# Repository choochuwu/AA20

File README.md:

# AA20
unsplit ortholinear "gaming" keyboard.
Like it's name sake, this isn't the greatest, but to me it is more comfortable for games compared to a column staggered board.

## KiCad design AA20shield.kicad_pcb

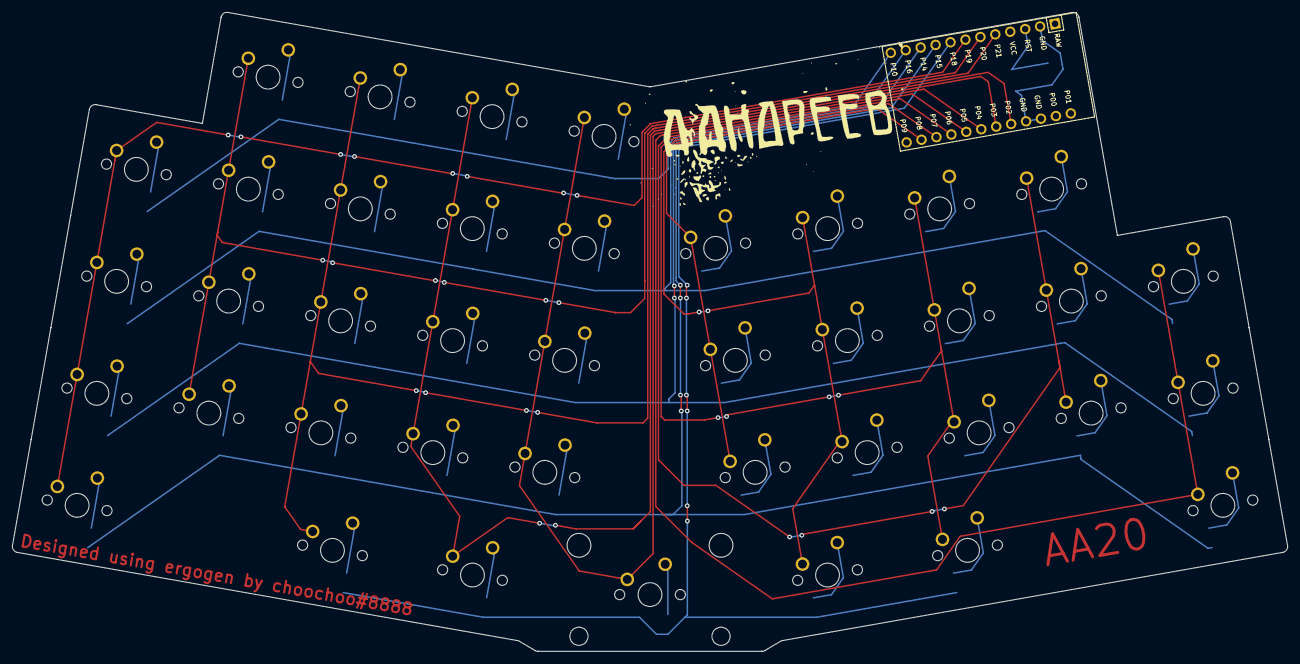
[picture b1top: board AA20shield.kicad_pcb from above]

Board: 2 copper layers, 213.6 x 107.0 mm, 82 parts (0 on the bottom side), 56 nets.

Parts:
B1: SW_TACT_ALPS_SKQGABE010
D1, D2, D3, D4, D5, D6, D7, D8, D9, D10, D11, D12, D13, D14, D15, D16, D17, D18, D19, D20, D21, D22, D23, D24, D25, D26, D27, D28, D29, D30, D31, D32, D33, D34, D35, D36, D37, D38, D39, D40: ComboDiode
MCU1: ProMicro
S1, S2, S3, S4, S5, S6, S7, S8, S9, S10, S11, S12, S13, S14, S15, S16, S17, S18, S19, S20, S21, S22, S23, S24, S25, S26, S27, S28, S29, S30, S31, S32, S33, S34, S35, S36, S37, S38, S39, S40: MX

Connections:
GND: B1.2, MCU1.2, MCU1.15, MCU1.16
P2: MCU1.17, S13.2, S14.2, S15.2, S16.2, S22.2
P3: MCU1.18, S17.2, S18.2, S19.2, S20.2, S23.2
P4: MCU1.19, S24.2, S25.2, S26.2
P5: MCU1.20, S27.2, S28.2, S29.2
P6: MCU1.21, S30.2, S31.2, S32.2, S39.2
P7: MCU1.22, S33.2, S34.2, S35.2, S40.2
P8: MCU1.23, S36.2, S37.2, S38.2
P10: D4.1, D8.1, D12.1, D16.1, D20.1, MCU1.12
P14: D2.1, D6.1, D10.1, D14.1, D18.1, D25.1, D28.1, D31.1, D34.1, D37.1, MCU1.10
P15: D1.1, D5.1, D9.1, D13.1, D17.1, D24.1, D27.1, D30.1, D33.1, D36.1, MCU1.9
P16: D3.1, D7.1, D11.1, D15.1, D19.1, D26.1, D29.1, D32.1, D35.1, D38.1, MCU1.11
P18: D21.1, D22.1, D23.1, D39.1, D40.1, MCU1.8
P19: MCU1.7, S1.2, S2.2, S3.2, S4.2
P20: MCU1.6, S5.2, S6.2, S7.2, S8.2
P21: MCU1.5, S9.2, S10.2, S11.2, S12.2, S21.2
RST: B1.1, MCU1.3
center_only: D22.2, D23.2, S22.1, S23.1
index_bottom: D13.2, S13.1
index_home: D14.2, S14.1
index_number: D16.2, S16.1
index_top: D15.2, S15.1
inner_bottom: D17.2, S17.1
inner_home: D18.2, S18.1
inner_number: D20.2, S20.1
inner_top: D19.2, S19.1
middle_bottom: D9.2, S9.1
middle_home: D10.2, S10.1
middle_number: D12.2, S12.1
middle_top: D11.2, S11.1
mirror_center_only: D40.2, S40.1
mirror_index_bottom: D33.2, S33.1
mirror_index_home: D34.2, S34.1
mirror_index_top: D35.2, S35.1
mirror_inner_bottom: D36.2, S36.1
mirror_inner_home: D37.2, S37.1
mirror_inner_top: D38.2, S38.1
mirror_middle_bottom: D30.2, S30.1
mirror_middle_home: D31.2, S31.1
mirror_middle_top: D32.2, S32.1
mirror_pinky_bottom: D24.2, S24.1
mirror_pinky_home: D25.2, S25.1
mirror_pinky_top: D26.2, S26.1
mirror_ring_bottom: D27.2, S27.1
mirror_ring_home: D28.2, S28.1
mirror_ring_top: D29.2, S29.1
mirror_tuck_only: D39.2, S39.1
pinky_bottom: D1.2, S1.1
pinky_home: D2.2, S2.1
pinky_number: D4.2, S4.1
pinky_top: D3.2, S3.1
ring_bottom: D5.2, S5.1
ring_home: D6.2, S6.1
ring_number: D8.2, S8.1
ring_top: D7.2, S7.1
tuck_only: D21.2, S21.1

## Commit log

2021-12-04 zmk files
